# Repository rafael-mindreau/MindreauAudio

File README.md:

# Mindreau Audio

This repository consists of all open-source Eurorack modules created and designed by @rafael-mindreau for the community. Feel free fork this and make it your own. All modules have their own build docs.

## Modules in this package
* Octane

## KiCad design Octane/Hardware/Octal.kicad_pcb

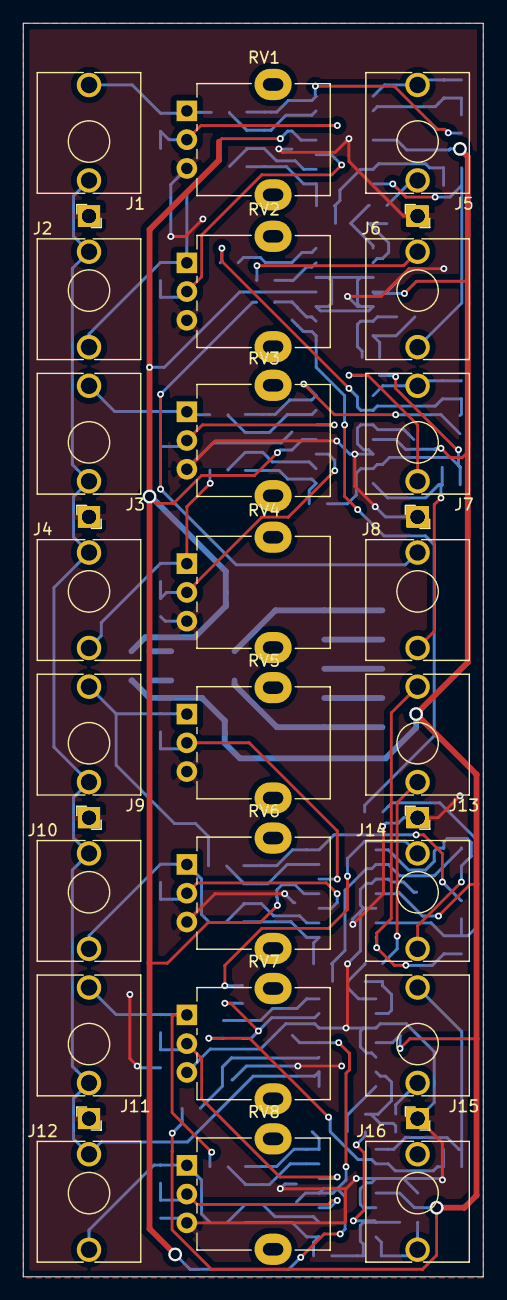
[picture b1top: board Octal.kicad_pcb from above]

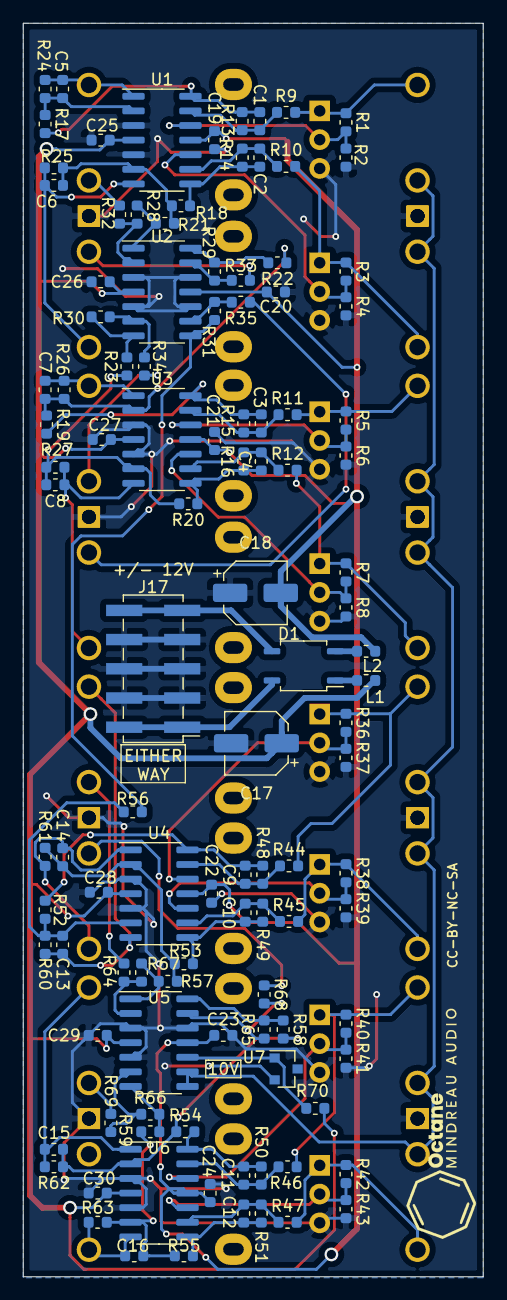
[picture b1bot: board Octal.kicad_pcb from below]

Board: 2 copper layers, 40.0 x 109.0 mm, 136 parts (112 on the bottom side), 78 nets.

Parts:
C1, C2, C3, C4, C5, C6, C7, C8, C9, C10, C11, C12, C13, C14, C15, C16: 10pF; C_0603_1608Metric
C17, C18: 10µF; CP_Elec_5x5.4
C19, C20, C21, C22, C23, C24, C25, C26, C27, C28, C29, C30: 100n; C_0603_1608Metric
D1: MB1S; SOP-4_3.8x4.1mm_P2.54mm
J1, J2, J3, J4, J5, J6, J7, J8, J9, J10, J11, J12, J13, J14, J15, J16: WQP-PJ301M-12_JACK; Jack_3.5mm_QingPu_WQP-PJ398SM_Vertical_CircularHoles
J17: EURORACK CONNECTOR; PinHeader_2x05_P2.54mm_Vertical_SMD
L1, L2: Ferrite_Bead; L_0603_1608Metric
R1, R2, R3, R4, R5, R6, R7, R8, R36, R37, R38, R39, R40, R41, R42, R43: 47k; R_0603_1608Metric
R9, R10, R11, R12, R13, R14, R15, R16, R17, R18, R19, R20, R21, R22, R23, R24, R25, R26, R27, R28, R29, R30, R31, R32, R33, R34, R35, R44, R45, R46, R47, R48, R49, R50, R51, R52, R53, R54, R55, R56, R57, R58, R59, R60, R61, R62, R63, R64, R65, R66, R67, R68, R69: 100k; R_0603_1608Metric
R70: 10k; R_0603_1608Metric
RV1, RV2, RV3, RV4, RV5, RV6, RV7, RV8: 100k; Potentiometer_Alpha_RD901F-40-00D_Single_Vertical
Ref**: Val**; drawing
U1, U2, U3, U4, U5, U6: TL074; SOIC-14_3.9x8.7mm_P1.27mm
U7: LM4040DBZ-10; SOT-23

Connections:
10V: J1.2, J2.2, J3.2, J4.2, J9.2, J10.2, J11.2, J12.2, U5.8, U5.9
CHAIN_1: R21.1, R28.2, U2.1
CHAIN_2: R22.1, R29.2, U2.14
CHAIN_3: R23.1, R30.2, U2.7
CHAIN_4: R31.2, R56.1, U2.8
CHAIN_5: R57.1, R64.2, U5.1
CHAIN_6: R58.1, R65.2, U5.14
CHAIN_7: R59.1, R66.2, U5.7
GND: C17.2, C18.1, C19.1, C20.1, C21.1, C22.1, C23.1, C24.1, C25.2, C26.2, C27.2, C28.2, C29.2, C30.2, J1.1, J2.1, J3.1, J4.1, J5.1, J6.1, J7.1, J8.1, J9.1, J10.1, J11.1, J12.1, J13.1, J14.1, J15.1, J16.1, J17.3, J17.4, J17.5, J17.6, J17.7, J17.8, R2.2, R4.2, R6.2, R8.2, R37.2, R39.2, R41.2, R43.2, RV1.3, RV2.3, RV3.3, RV4.3, RV5.3, RV6.3, RV7.3, RV8.3, U1.3, U1.5, U2.3, U2.5, U2.10, U2.12, U3.3, U3.5, U4.3, U4.5, U5.3, U5.5, U5.12, U6.3, U6.5, U7.2
unnamed: C1.1, R13.1, R17.2, U1.14
unnamed: C1.2, R9.1, R13.2, U1.13
unnamed: C2.1, R14.1, R18.2, U1.8
unnamed: C2.2, R10.1, R14.2, U1.9
unnamed: C3.1, R15.1, R19.2, U3.14
unnamed: C3.2, R11.1, R15.2, U3.13
unnamed: C4.1, R16.1, R20.2, U3.8
unnamed: C4.2, R12.1, R16.2, U3.9
unnamed: C5.1, J5.3, R24.1, U1.1
unnamed: C5.2, R17.1, R24.2, U1.2
unnamed: C6.1, J6.3, R25.1, U1.7
unnamed: C6.2, R18.1, R21.2, R25.2, U1.6
unnamed: C7.1, J7.3, R26.1, U3.1
unnamed: C7.2, R19.1, R22.2, R26.2, U3.2
unnamed: C8.1, J8.3, R27.1, U3.7
unnamed: C8.2, R20.1, R23.2, R27.2, U3.6
unnamed: C9.1, R48.1, R52.2, U4.14
unnamed: C9.2, R44.1, R48.2, U4.13
unnamed: C10.1, R49.1, R53.2, U4.8
unnamed: C10.2, R45.1, R49.2, U4.9
unnamed: C11.1, R50.1, R54.2, U6.14
unnamed: C11.2, R46.1, R50.2, U6.13
unnamed: C12.1, R51.1, R55.2, U6.8
unnamed: C12.2, R47.1, R51.2, U6.9
unnamed: C13.1, J13.3, R60.1, U4.7
unnamed: C13.2, R52.1, R56.2, R60.2, U4.6
unnamed: C14.1, J14.3, R61.1, U4.1
unnamed: C14.2, R53.1, R57.2, R61.2, U4.2
unnamed: C15.1, J15.3, R62.1, U6.1
unnamed: C15.2, R54.1, R58.2, R62.2, U6.2
unnamed: C16.1, J16.3, R63.1, U6.7
unnamed: C16.2, R55.1, R59.2, R63.2, U6.6
unnamed: D1.1, L1.2
unnamed: D1.2, L2.2
unnamed: D1.3, J17.9, J17.10
unnamed: D1.4, J17.1, J17.2
unnamed: J1.3, R1.1, R9.2, RV1.1
unnamed: J2.3, R3.1, R10.2, RV2.1
unnamed: J3.3, R5.1, R11.2, RV3.1
unnamed: J4.3, R7.1, R12.2, RV4.1
unnamed: J5.2, R32.1
unnamed: J6.2, R33.1
unnamed: J7.2, R34.1
unnamed: J8.2, R35.1
unnamed: J9.3, R36.1, R44.2, RV5.1
unnamed: J10.3, R38.1, R45.2, RV6.1
unnamed: J11.3, R40.1, R46.2, RV7.1
unnamed: J12.3, R42.1, R47.2, RV8.1
unnamed: J13.2, R67.1
unnamed: J14.2, R68.1
unnamed: J15.2, R69.1
unnamed: R1.2, R2.1, RV1.2, U1.12
unnamed: R3.2, R4.1, RV2.2, U1.10
unnamed: R5.2, R6.1, RV3.2, U3.12
unnamed: R7.2, R8.1, RV4.2, U3.10
unnamed: R28.1, R32.2, U2.2
unnamed: R29.1, R33.2, U2.13
unnamed: R30.1, R34.2, U2.6
unnamed: R31.1, R35.2, U2.9
unnamed: R36.2, R37.1, RV5.2, U4.12
unnamed: R38.2, R39.1, RV6.2, U4.10
unnamed: R40.2, R41.1, RV7.2, U6.12
unnamed: R42.2, R43.1, RV8.2, U6.10
unnamed: R64.1, R67.2, U5.2
unnamed: R65.1, R68.2, U5.13
unnamed: R66.1, R69.2, U5.6
unnamed: R70.2, U5.10, U7.1
VCC: C17.1, C25.1, C26.1, C27.1, C28.1, C29.1, C30.1, L1.1, R70.1, U1.4, U2.4, U3.4, U4.4, U5.4, U6.4
VEE: C18.2, C19.2, C20.2, C21.2, C22.2, C23.2, C24.2, L2.1, U1.11, U2.11, U3.11, U4.11, U5.11, U6.11

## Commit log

2022-01-17 Started versioning this project
2023-04-22 Some re-organizing and extra README
2023-04-22 Add new folder structure
2023-04-22 Added image to Philberg README
2023-06-21 Fixed overlapping trace with pad of C17

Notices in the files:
Octane/Hardware/Octal.kicad_pcb:
License: CC-BY-NC-SA
CC-BY-NC-SA
